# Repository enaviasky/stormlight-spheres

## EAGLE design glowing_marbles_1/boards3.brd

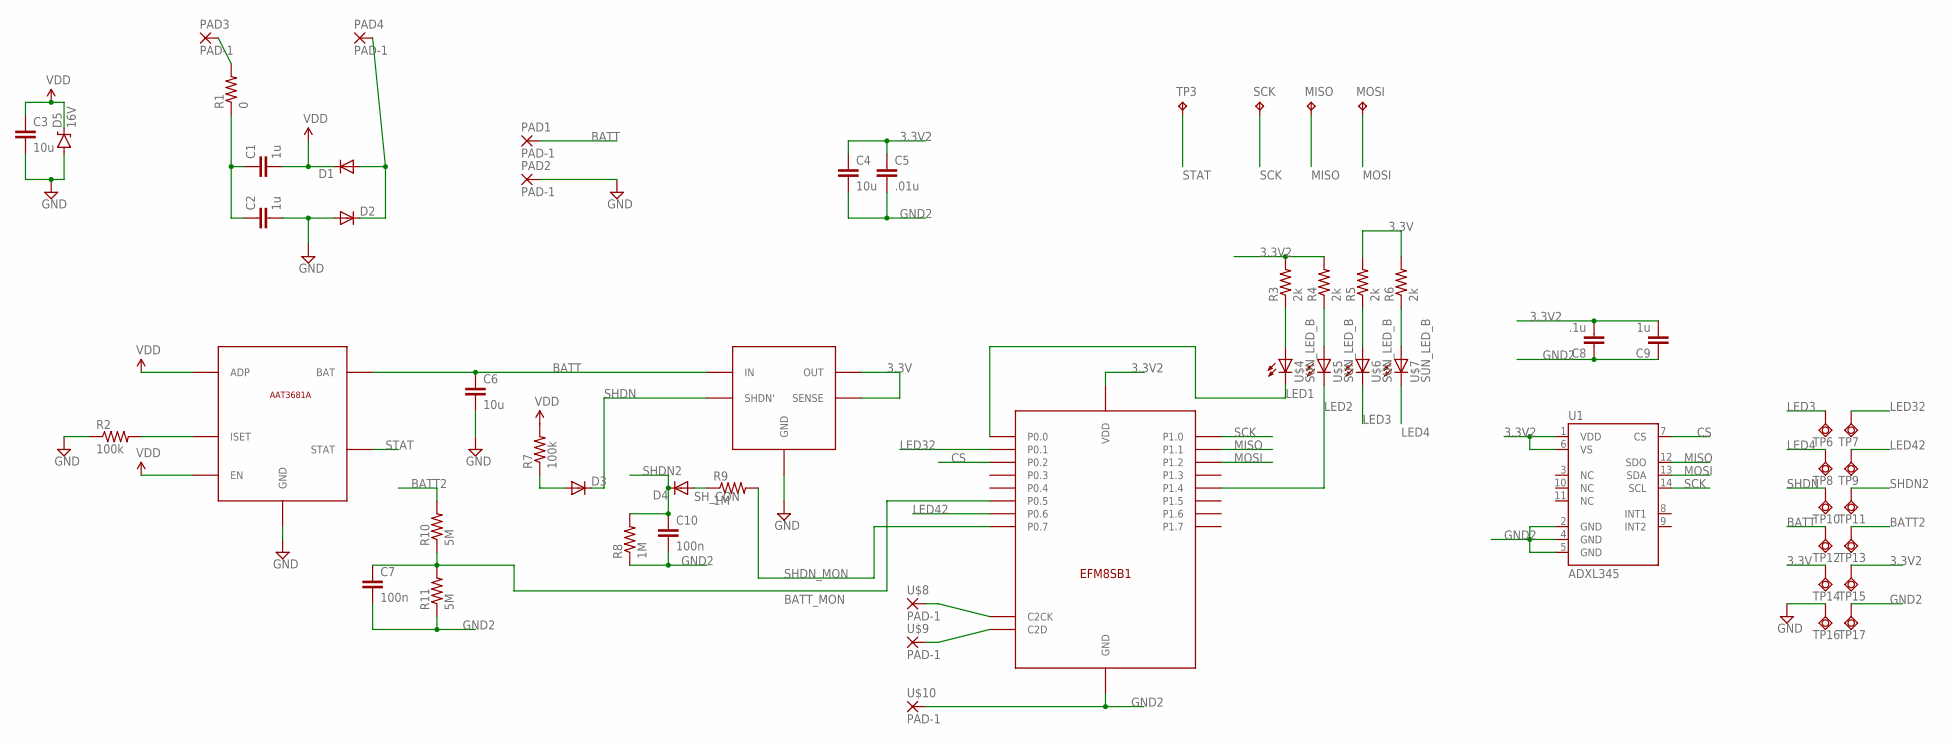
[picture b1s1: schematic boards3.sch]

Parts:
C1, C2, C9: 1u; 0402-CAP
C3, C4, C6: 10u; 0603-CAP
C5: .01u; 0402-CAP
C7, C10: 100n; 0402-CAP
C8: .1u; 0402-CAP
D1, D2, D3, D4: DIODE-SOD323-W; SOD323-W
D5: 16V; SOD-123
MISO: TPB1,27; B1,27
MOSI: TPB1,27; B1,27
PAD1, PAD2, PAD3, PAD4: PAD-1; PAD
R1: 0; 0402-RES
R2, R7: 100k; 0402-RES
R3, R4, R5, R6: 2k; 0402-RES
R8, R9: 1M; 0402-RES
R10, R11: 5M; 0402-RES
SCK: TPB1,27; B1,27
TP3: TPB1,27; B1,27
TP6, TP7, TP8, TP9, TP10, TP11, TP12, TP13, TP14, TP15, TP16, TP17: TPSQB1,27; B1,27
U1: ADXL345; LGA14
U$1: AAT3681A; SC70JW-8
U$2: EFM8SB1
U$3: LT3008; TSOT23-8
U$4, U$5, U$6, U$7: SUN_LED_B; 1209
U$8, U$9, U$10: PAD-1; PAD

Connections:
3.3V: R5.2, R6.2, TP14.TP, U$3.6 (OUT), U$3.7 (SENSE)
3.3V2: C4.1, C5.1, C8.2, C9.2, R3.2, R4.2, TP15.TP, U1.1 (VDD), U1.6 (VS), U$2.3 (VDD)
BATT: C6.1, PAD1.P$1, TP12.TP, U$1.3 (BAT), U$3.5 (IN)
BATT2: R10.2, TP13.TP
BATT_MON: C7.1, R10.1, R11.2, U$2.19 (P0.5)
C2CK: U$2.6 (C2CK), U$8.P$1
C2D: U$2.7 (C2D), U$9.P$1
CS: U1.7 (CS), U$2.22 (P0.2)
GND: C2.2, C3.2, C6.2, D2.A, D5.A, PAD2.P$1, R2.1, TP16.TP, U$1.6 (GND), U$1.7 (GND), U$1.8 (GND), U$3.2 (GND), U$3.3 (GND), U$3.4 (GND)
GND2: C4.2, C5.2, C7.2, C8.1, C9.1, C10.2, R8.1, R11.1, TP17.TP, U1.2 (GND), U1.4 (GND), U1.5 (GND), U$2.2 (GND), U$10.P$1
LED1: U$2.24 (P0.0), U$4.C
LED2: U$2.12 (P1.4), U$5.C
LED3: TP6.TP, U$6.C
LED4: TP8.TP, U$7.C
LED32: TP7.TP, U$2.23 (P0.1)
LED42: TP9.TP, U$2.18 (P0.6)
MISO: MISO.TP, U1.12 (SDO), U$2.15 (P1.1)
MOSI: MOSI.TP, U1.13 (SDA), U$2.14 (P1.2)
unnamed: R2.2, U$1.2 (ISET)
unnamed: R3.1, U$4.A
unnamed: D3.A, R7.1
unnamed: R4.1, U$5.A
unnamed: R5.1, U$6.A
unnamed: R6.1, U$7.A
unnamed: C1.1, C2.1, R1.1
unnamed: D1.A, D2.C, PAD4.P$1
unnamed: PAD3.P$1, R1.2
SCK: SCK.TP, U1.14 (SCL), U$2.16 (P1.0)
SHDN: D3.C, TP10.TP, U$3.1 (SHDN')
SHDN2: C10.1, D4.C, R8.2, TP11.TP
SHDN_MON: R9.2, U$2.17 (P0.7)
SH_CON: D4.A, R9.1
STAT: TP3.TP, U$1.5 (STAT)
VDD: C1.2, C3.1, D1.C, D5.C, R7.2, U$1.1 (EN), U$1.4 (ADP)

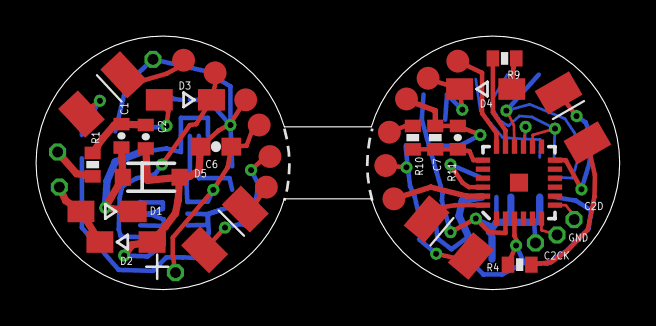
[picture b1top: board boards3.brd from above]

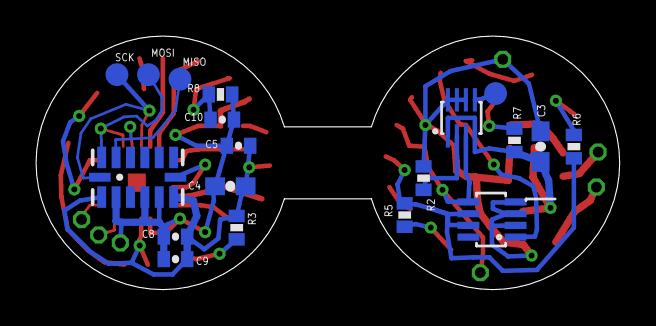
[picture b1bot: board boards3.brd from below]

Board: 2 copper layers, 32.4 x 14.1 mm, 57 parts (19 on the bottom side), 34 nets.

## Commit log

2016-05-23 eagle

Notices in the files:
parts and their libraries:
SparkFun-Passives: Licensing: Creative Commons ShareAlike 4.0 International - https://creativecommons.org/licenses/by-sa/4.0
